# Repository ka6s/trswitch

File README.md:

TR Switch

This is a clone of the HPSDR TR Switch found on TAPR.

There are only a couple of changes:

1) Can switch three antenna ports.
2) Has an adapter connector to work with my Break-out board.

This is NOT an impedance matched design - so buyer beware.

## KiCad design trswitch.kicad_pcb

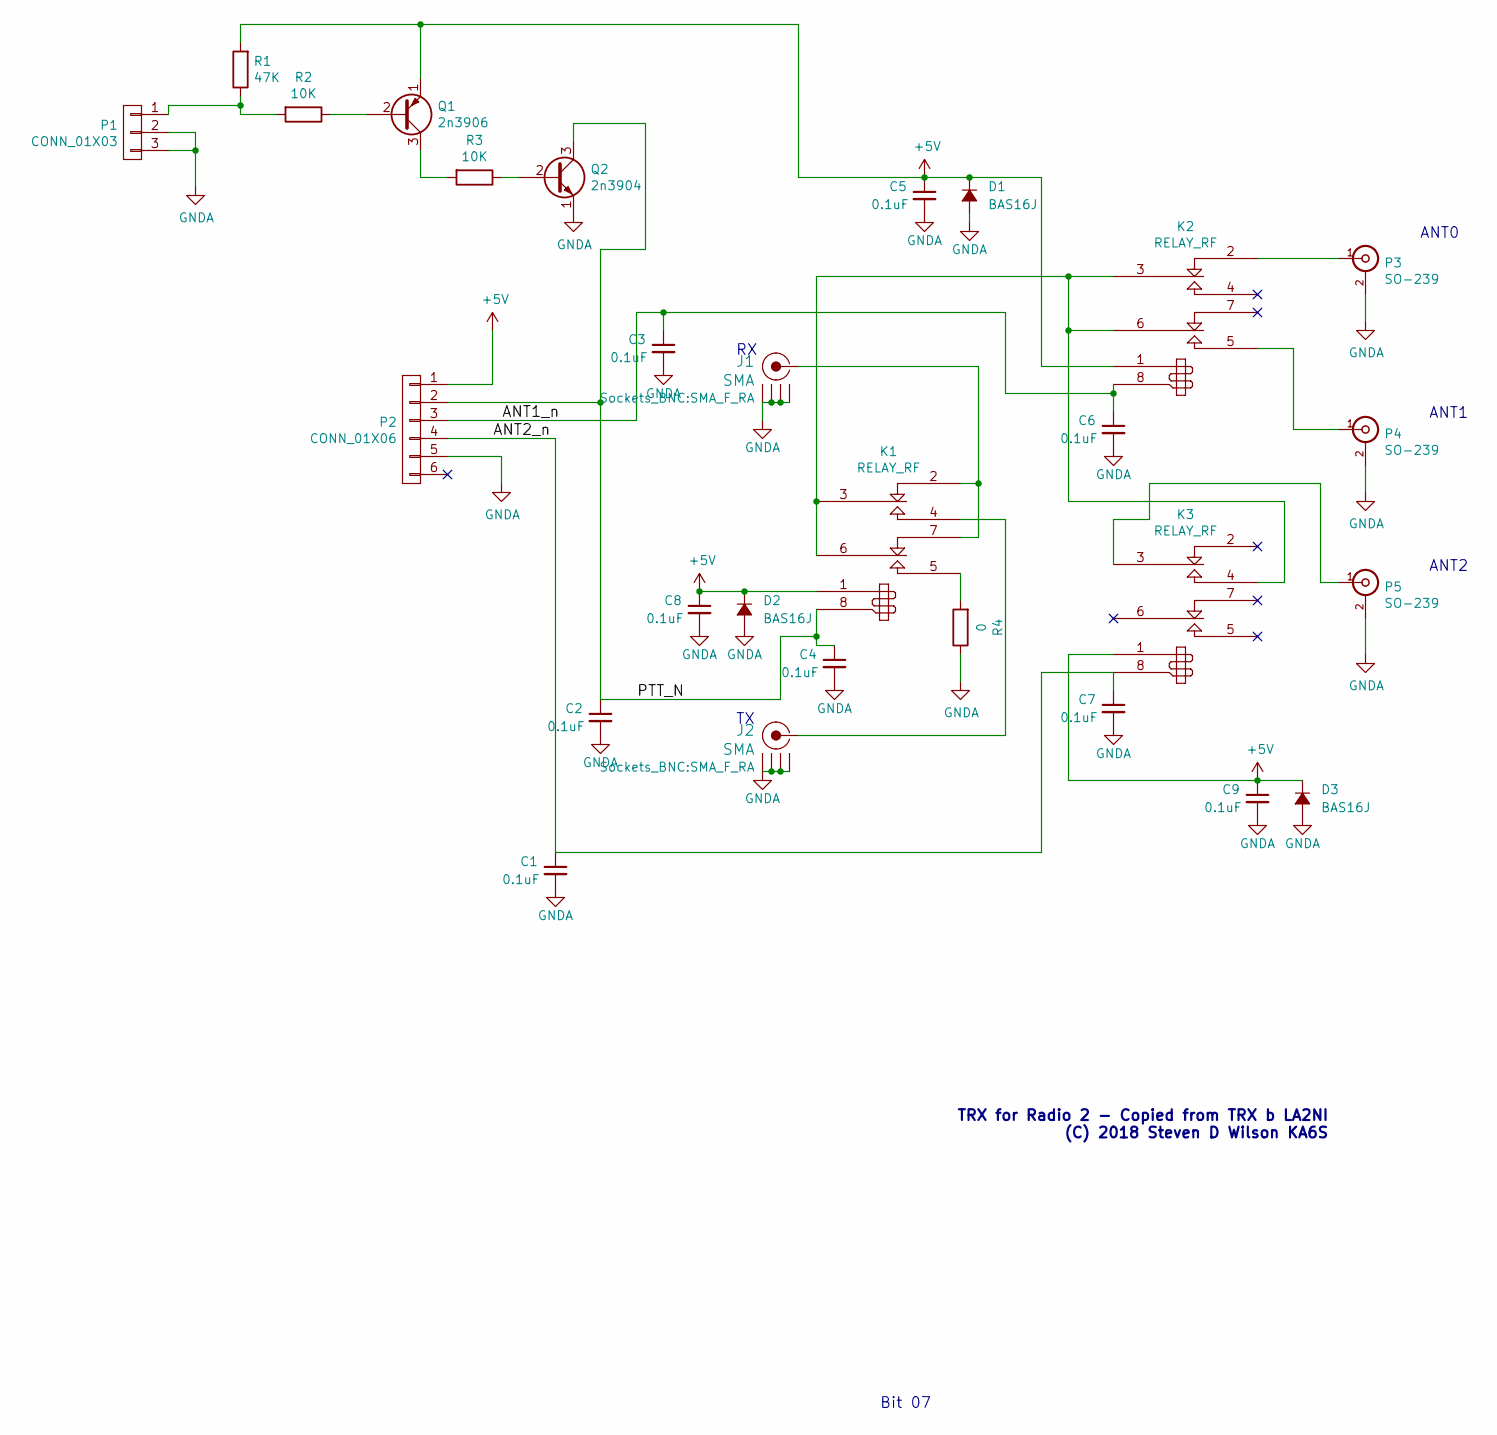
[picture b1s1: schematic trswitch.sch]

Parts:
C1, C2, C3, C4, C5, C6, C7, C8, C9: 0.1uF; C_1206_HandSoldering
D1, D2, D3: BAS16J; SMA_Handsoldering
J1, J2: SMA; SMA_F_RA
K1, K2, K3: RELAY_RF; G6J-2P-Y
P1: CONN_01X03; Pin_Header_Straight_1x03
P2: CONN_01X06; Socket_Strip_Angled_1x06
P3, P4, P5: SO-239
Q1: 2n3906; TO-92_Inline_Narrow_Oval
Q2: 2n3904; TO-92_Inline_Narrow_Oval
R1: 47K; R_1206
R2, R3: 10K; R_1206
R4: 0; R_1206

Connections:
+5V: C5.1, C8.1, C9.1, D1.1 (K), D2.1 (K), D3.1 (K), K1.1 (8), K2.1 (8), K3.1 (8), P2.1, Q1.1 (E), R1.2
/ANT1_n: C3.1, C6.1, K2.8 (9), P2.3
/ANT2_n: C1.1, C7.1, K3.8 (9), P2.4
/PTT_N: C2.1, C4.1, K1.8 (9), P2.2, Q2.3 (C)
GNDA: C1.2, C2.2, C3.2, C4.2, C5.2, C6.2, C7.2, C8.2, C9.2, D1.2 (A), D2.2 (A), D3.2 (A), J1.2 (GND1), J1.3 (GND2), J1.4 (GND3), J1.5 (GND4), J2.2 (GND1), J2.3 (GND2), J2.4 (GND3), J2.5 (GND4), P1.2, P1.3, P2.5, P3.2 (Ext), P4.2 (Ext), P5.2 (Ext), Q2.1 (E), R4.1
unnamed: J1.1 (RF), K1.2 (R2), K1.7 (R1)
unnamed: J2.1 (RF), K1.4 (T2)
unnamed: K1.3 (C2), K1.6 (C1), K2.3 (C2), K2.6 (C1), K3.4 (T2)
unnamed: K1.5 (T1), R4.2
unnamed: K2.2 (R2), P3.1 (In)
unnamed: K2.5 (T1), P4.1 (In)
unnamed: K3.3 (C2), P5.1 (In)
unnamed: P1.1, R1.1, R2.2
unnamed: Q1.2 (B), R2.1
unnamed: Q1.3 (C), R3.2
unnamed: Q2.2 (B), R3.1

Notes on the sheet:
TRX for Radio 2 - Copied from TRX b LA2NI (C) 2018 Steven D Wilson KA6S
Bit 07
ANT0
ANT1
ANT2

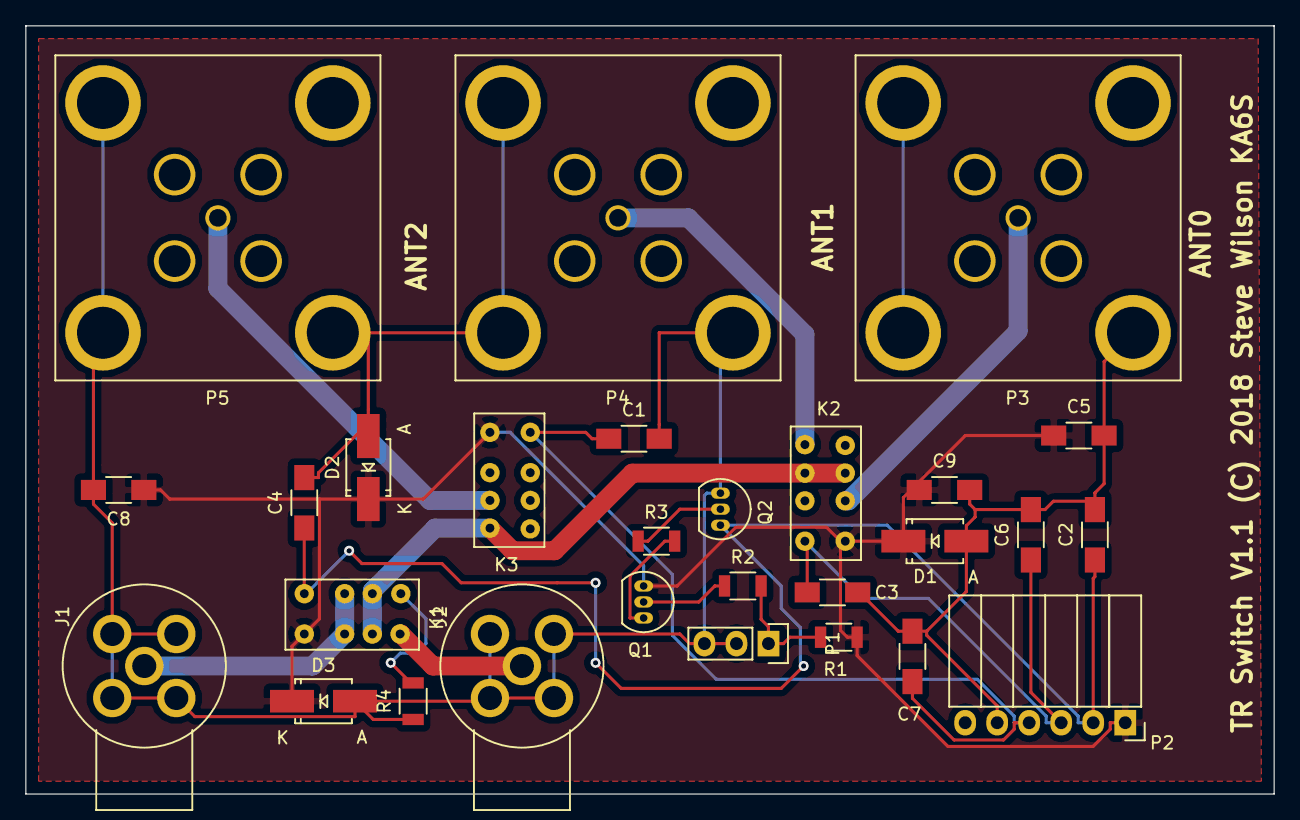
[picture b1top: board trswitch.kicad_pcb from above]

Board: 2 copper layers, 99.1 x 61.0 mm, 28 parts (0 on the bottom side), 16 nets.

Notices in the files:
trswitch.kicad_pcb:
TR Switch V1.1 (C) 2018 Steve Wilson KA6S
